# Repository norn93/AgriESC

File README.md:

# AgriESC
A brushless motor driver for small to medium sized motors

This project was forked from and inspired by antonchromjak's MINI4 (Mini VESC: https://github.com/antonchromjak/MINI4) and was practically copied from Benjamin Vedder's Brushless Motor Controller (VESC: https://github.com/vedderb/bldc-hardware). It is an attempt to build a slightly cheaper motor controller for 24 V/10 A motors.

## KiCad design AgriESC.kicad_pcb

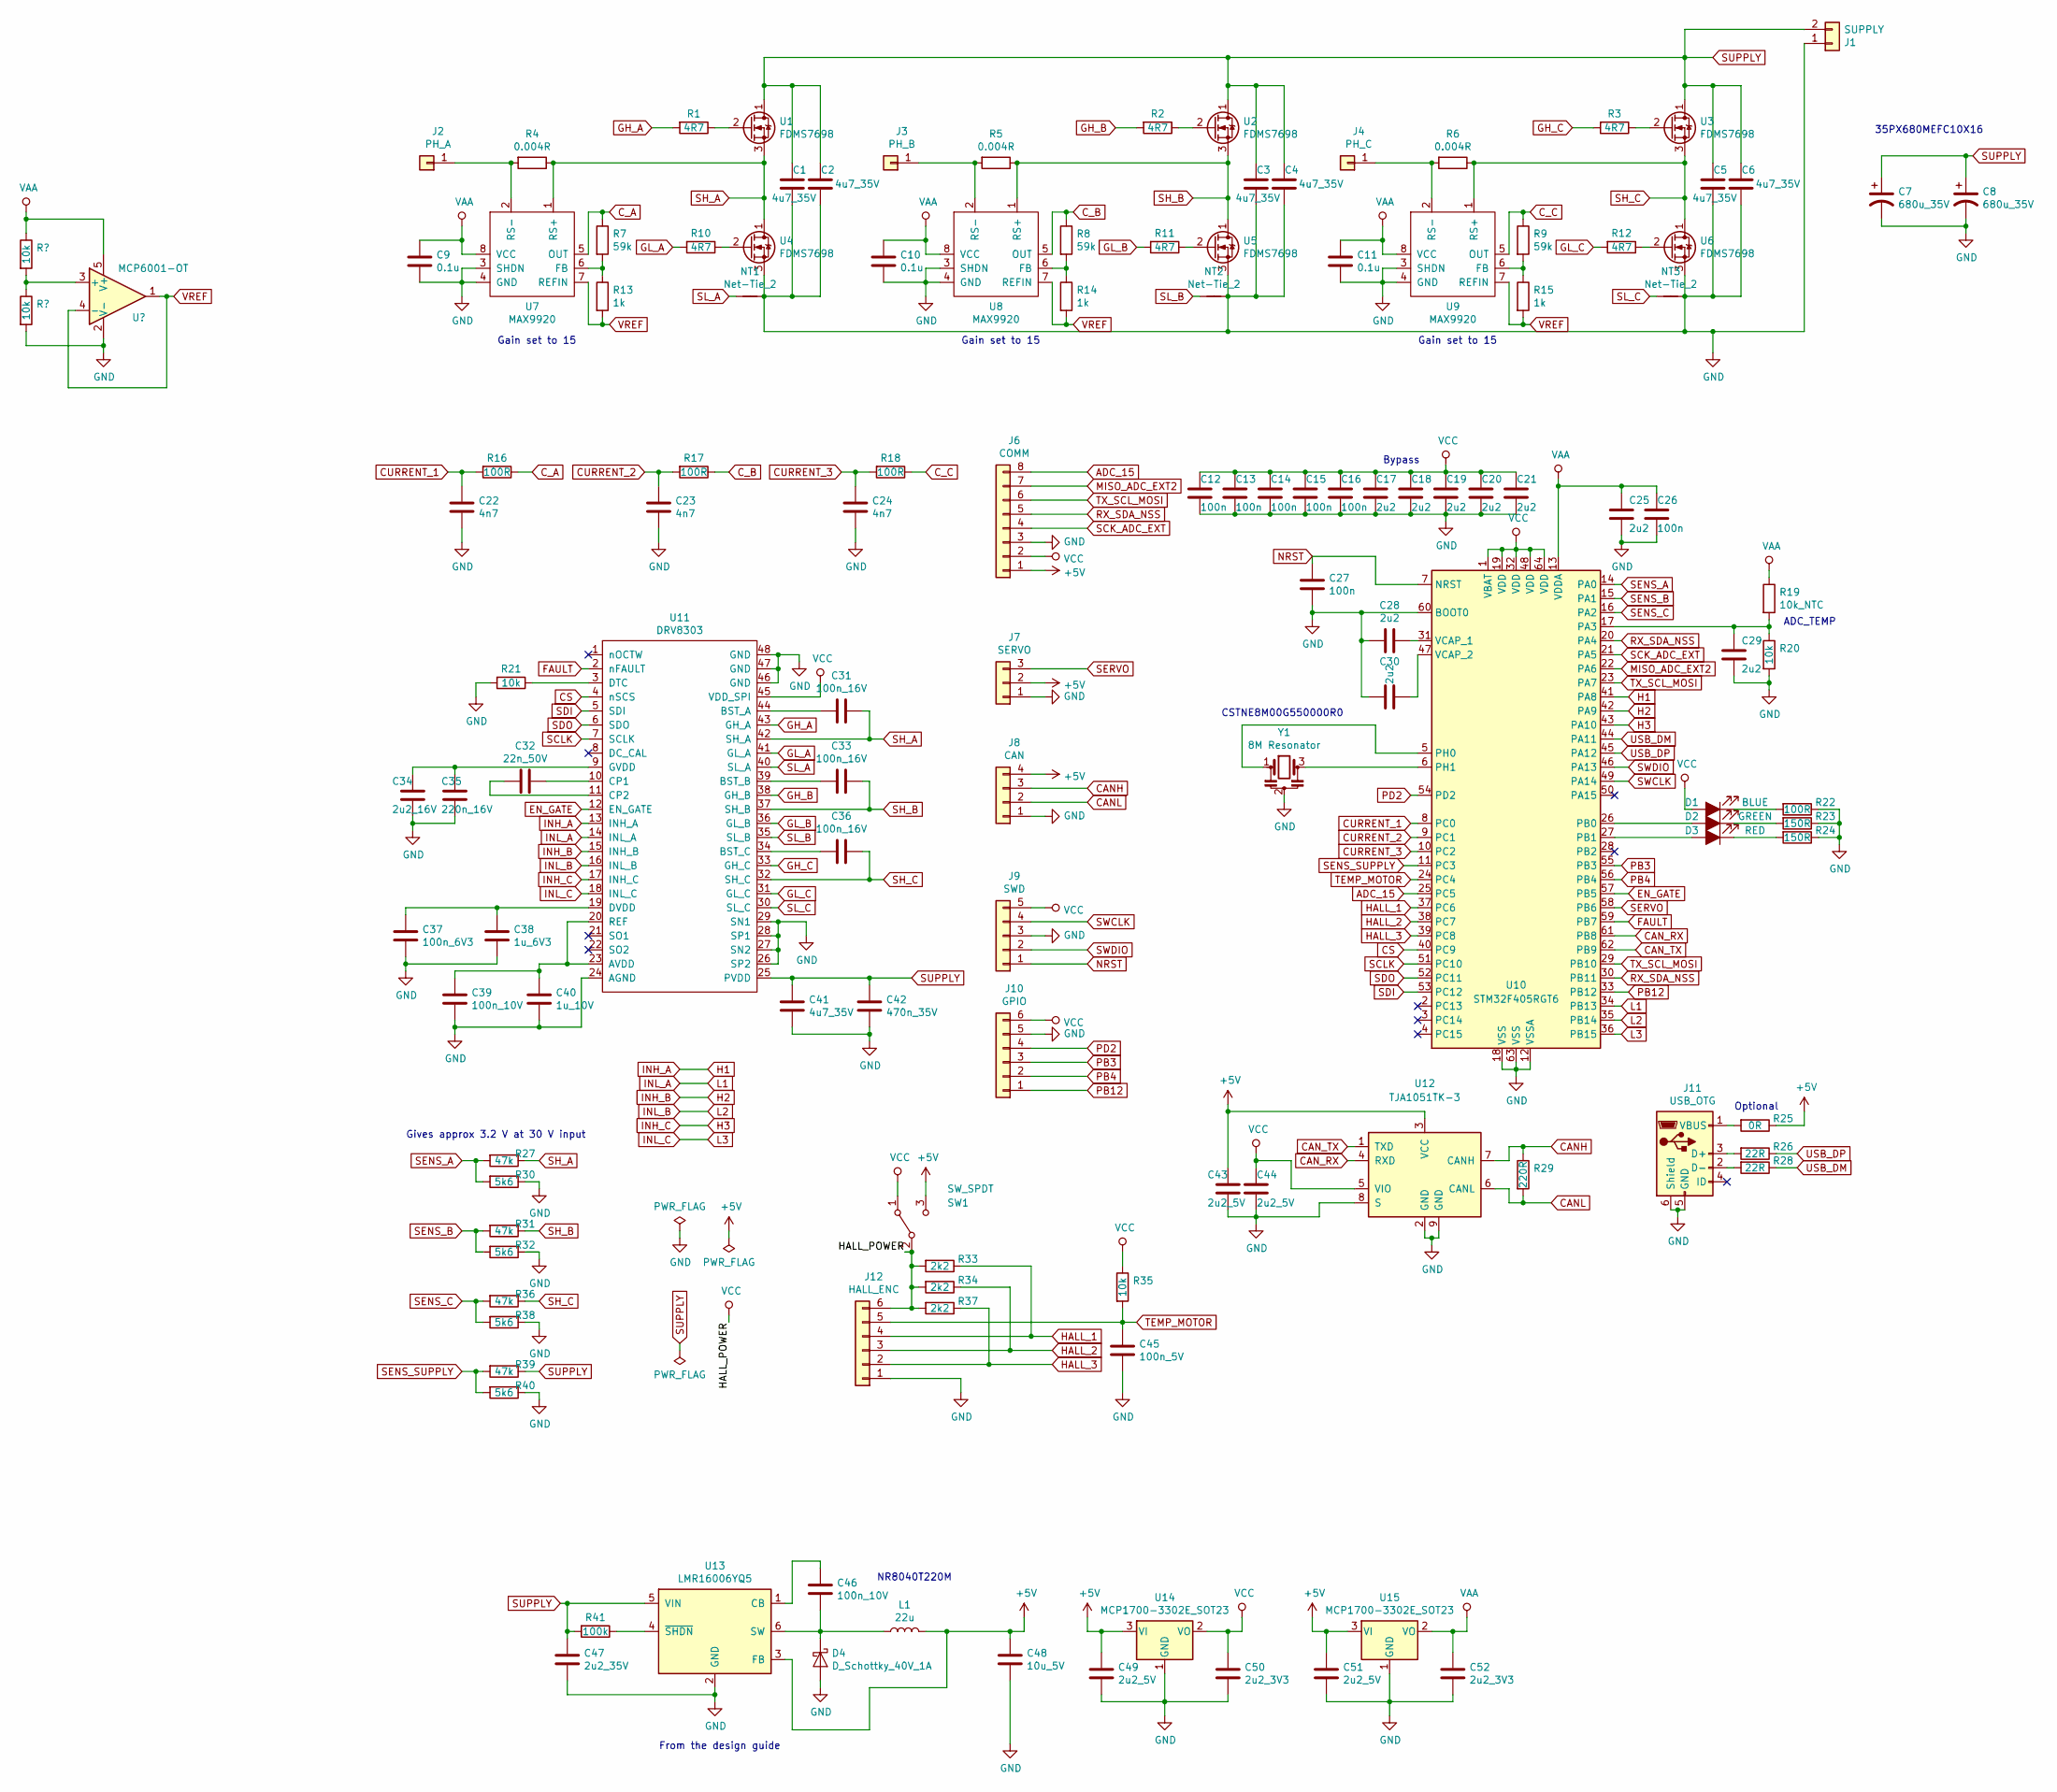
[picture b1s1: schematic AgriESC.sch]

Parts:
C1, C2, C3, C4, C5, C6, C41: 4u7_35V; C_0805_2012Metric_Pad1.15x1.40mm_HandSolder
C7, C8: 680u_35V; CP_Radial_D10.0mm_P5.00mm_Side_Mounted
C9, C10, C11: 0.1u; C_0603_1608Metric_Pad1.05x0.95mm_HandSolder
C12, C13, C14, C15, C16, C26, C27: 100n; C_0603_1608Metric_Pad1.05x0.95mm_HandSolder
C17, C18, C19, C20, C21, C25, C28, C29, C30: 2u2; C_0603_1608Metric_Pad1.05x0.95mm_HandSolder
C22, C23, C24: 4n7; C_0603_1608Metric_Pad1.05x0.95mm_HandSolder
C31, C33, C36: 100n_16V; C_0603_1608Metric_Pad1.05x0.95mm_HandSolder
C32: 22n_50V; C_0603_1608Metric_Pad1.05x0.95mm_HandSolder
C34: 2u2_16V; C_0603_1608Metric_Pad1.05x0.95mm_HandSolder
C35: 220n_16V; C_0603_1608Metric_Pad1.05x0.95mm_HandSolder
C37: 100n_6V3; C_0603_1608Metric_Pad1.05x0.95mm_HandSolder
C38: 1u_6V3; C_0603_1608Metric_Pad1.05x0.95mm_HandSolder
C39, C46: 100n_10V; C_0603_1608Metric_Pad1.05x0.95mm_HandSolder
C40: 1u_10V; C_0603_1608Metric_Pad1.05x0.95mm_HandSolder
C42: 470n_35V; C_0603_1608Metric_Pad1.05x0.95mm_HandSolder
C43, C44, C49, C51: 2u2_5V; C_0603_1608Metric_Pad1.05x0.95mm_HandSolder
C45: 100n_5V; C_0603_1608Metric_Pad1.05x0.95mm_HandSolder
C47: 2u2_35V; C_0603_1608Metric_Pad1.05x0.95mm_HandSolder
C48: 10u_5V; C_0603_1608Metric_Pad1.05x0.95mm_HandSolder
C50, C52: 2u2_3V3; C_0603_1608Metric_Pad1.05x0.95mm_HandSolder
D1: BLUE; LED_0603_1608Metric_Pad1.05x0.95mm_HandSolder
D2: GREEN; LED_0603_1608Metric_Pad1.05x0.95mm_HandSolder
D3: RED; LED_0603_1608Metric_Pad1.05x0.95mm_HandSolder
D4: D_Schottky_40V_1A; D_SOD-123F
J1: SUPPLY; XT30PW-F
J2: PH_A; SolderWirePad_1x01_SMD_5x10mm
J3: PH_B; SolderWirePad_1x01_SMD_5x10mm
J4: PH_C; SolderWirePad_1x01_SMD_5x10mm
J6: COMM; JST_PA_01x08
J7: SERVO; JST_PA_01x03
J8: CAN; JST_PA_01x04
J9: SWD; JST_PA_01x05
J10: GPIO; JST_PA_01x06
J11: USB_OTG; CONN-10118194-0001LF-FCI3
J12: HALL_ENC; JST_PA_01x06
L1: 22u; NR8040T220M
NT1, NT2, NT3: Net-Tie_2; NetTie-2_SMD_Pad0.5mm
R1, R2, R3, R10, R11, R12: 4R7; R_0603_1608Metric_Pad1.05x0.95mm_HandSolder
R4, R5, R6: 0.004R; R_2512_6332Metric_Pad1.52x3.35mm_HandSolder
R7, R8, R9: 59k; R_0603_1608Metric_Pad1.05x0.95mm_HandSolder
R13, R14, R15: 1k; R_0603_1608Metric_Pad1.05x0.95mm_HandSolder
R16, R17, R18, R22: 100R; R_0603_1608Metric_Pad1.05x0.95mm_HandSolder
R19: 10k_NTC; R_0603_1608Metric_Pad1.05x0.95mm_HandSolder
R20, R21, R35: 10k; R_0603_1608Metric_Pad1.05x0.95mm_HandSolder
R23, R24: 150R; R_0603_1608Metric_Pad1.05x0.95mm_HandSolder
R25: 0R; R_0603_1608Metric_Pad1.05x0.95mm_HandSolder
R26, R28: 22R; R_0603_1608Metric_Pad1.05x0.95mm_HandSolder
R27, R31, R36, R39: 47k; R_0603_1608Metric_Pad1.05x0.95mm_HandSolder
R29: 220R; R_0603_1608Metric_Pad1.05x0.95mm_HandSolder
R30, R32, R38, R40: 5k6; R_0603_1608Metric_Pad1.05x0.95mm_HandSolder
R33, R34, R37: 2k2; R_0603_1608Metric_Pad1.05x0.95mm_HandSolder
R41: 100k; R_0603_1608Metric_Pad1.05x0.95mm_HandSolder
SW1: SW_SPDT; SolderJumper-3_P1.3mm_Open_RoundedPad1.0x1.5mm_NumberLabels
U1, U2, U3, U4, U5, U6: FDMS7698
U7, U8, U9: MAX9920
U10: STM32F405RGT6; LQFP-64_10x10mm_P0.5mm
U11: DRV8303
U12: TJA1051TK-3; DFN-8-1EP_3x3mm_Pitch0.65mm
U13: LMR16006YQ5; SOT-23-6
U14, U15: MCP1700-3302E_SOT23; SOT-23
Y1: 8M Resonator; CSTNE8M00G550000R0

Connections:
+5V: C43.1, C48.1, C49.1, C51.1, J6.1, J7.2, J8.4, L1.2, R25.1, SW1.3 (C), U12.3 (VCC), U13.3 (FB), U14.3 (VI), U15.3 (VI); also elsewhere on the board
ADC_15: J6.8, U10.25 (PC5); also elsewhere on the board
CANH: J8.3, R29.1, U12.7 (CANH); also elsewhere on the board
CANL: J8.2, R29.2, U12.6 (CANL); also elsewhere on the board
CAN_RX: U10.61 (PB8), U12.4 (RXD)
CAN_TX: U10.62 (PB9), U12.1 (TXD)
CS: U10.40 (PC9), U11.4 (nSCS)
CURRENT_1: C22.1, R16.2, U10.8 (PC0)
CURRENT_2: C23.1, R17.2, U10.9 (PC1)
CURRENT_3: C24.1, R18.2, U10.10 (PC2)
C_A: R7.1, R16.1, U7.5 (OUT)
C_B: R8.1, R17.1, U8.5 (OUT)
C_C: R9.1, R18.1, U9.5 (OUT)
EN_GATE: U10.57 (PB5), U11.12 (EN_GATE)
FAULT: U10.59 (PB7), U11.2 (nFAULT)
GH_A: R1.2, U11.43 (GH_A)
GH_B: R2.2, U11.38 (GH_B)
GH_C: R3.2, U11.33 (GH_C)
GL_A: R10.2, U11.41 (GL_A)
GL_B: R11.2, U11.36 (GL_B)
GL_C: R12.2, U11.31 (GL_C)
GND: C1.2, C2.2, C3.2, C4.2, C5.2, C6.2, C7.2, C8.2, C9.2, C10.2, C11.2, C12.2, C13.2, C14.2, C15.2, C16.2, C17.2, C18.2, C19.2, C20.2, C21.2, C22.2, C23.2, C24.2, C25.2, C26.2, C27.2, C28.2, C29.2, C30.2, C34.2, C35.2, C37.2, C38.2, C39.2, C40.2, C41.2, C42.2, C43.2, C44.2, C45.2, C47.2, C48.2, C49.2, C50.2, C51.2, C52.2, D4.2 (A), J1.1, J6.3, J7.1, J8.1, J9.3, J10.5, J11.5 (GND), J11.6 (Shield), J12.1, NT1.1, NT2.1, NT3.1, R20.2, R21.2, R22.1, R23.1, R24.1, R30.1, R32.1, R38.1, R40.1, U4.3 (S), U5.3 (S), U6.3 (S), U7.3 (SHDN), U7.4 (GND), U8.3 (SHDN), U8.4 (GND), U9.3 (SHDN), U9.4 (GND), U10.12 (VSSA), U10.18 (VSS), U10.60 (BOOT0), U10.63 (VSS), U11.24 (AGND), U11.26 (SP2), U11.27 (SN2), U11.28 (SP1), U11.29 (SN1), U11.46 (GND), U11.47 (GND), U11.48 (GND), U12.2 (GND), U12.8 (S), U12.9 (GND), U13.2 (GND), U14.1 (GND), U15.1 (GND), Y1.2; also elsewhere on the board
H1: U10.41 (PA8), U11.13 (INH_A)
H2: U10.42 (PA9), U11.15 (INH_B)
H3: U10.43 (PA10), U11.17 (INH_C)
HALL_1: J12.4, R33.1, U10.37 (PC6); also elsewhere on the board
HALL_2: J12.3, R34.1, U10.38 (PC7); also elsewhere on the board
HALL_3: J12.2, R37.1, U10.39 (PC8); also elsewhere on the board
INL_A: U10.34 (PB13), U11.14 (INL_A)
INL_B: U10.35 (PB14), U11.16 (INL_B)
INL_C: U10.36 (PB15), U11.18 (INL_C)
MISO_ADC_EXT2: J6.7, U10.22 (PA6); also elsewhere on the board
NRST: C27.1, J9.1, U10.7 (NRST); also elsewhere on the board
unnamed: C28.1, U10.31 (VCAP_1)
unnamed: C29.1, R19.2, R20.1, U10.17 (PA3)
unnamed: C30.1, U10.47 (VCAP_2)
unnamed: C31.2, U11.44 (BST_A)
unnamed: C32.1, U11.10 (CP1)
unnamed: C32.2, U11.11 (CP2)
unnamed: C33.2, U11.39 (BST_B)
unnamed: C34.1, C35.1, U11.9 (GVDD)
unnamed: C36.2, U11.34 (BST_C)
unnamed: C37.1, C38.1, U11.19 (DVDD)
unnamed: C39.1, C40.1, U11.20 (REF), U11.23 (AVDD)
unnamed: C46.1, D4.1 (K), L1.1, U13.6 (SW)
unnamed: C46.2, U13.1 (CB)
unnamed: D1.1 (K), R22.2
unnamed: D2.1 (K), R23.2
unnamed: D2.2 (A), U10.26 (PB0)
unnamed: D3.1 (K), R24.2
unnamed: D3.2 (A), U10.27 (PB1)
unnamed 51: J2.1, R4.2, U7.2 (RS-); also elsewhere on the board
unnamed 52: J3.1, R5.2, U8.2 (RS-); also elsewhere on the board
unnamed 53: J4.1, R6.2, U9.2 (RS-); also elsewhere on the board
unnamed 54: J11.1 (VBUS), R25.2; also elsewhere on the board
unnamed 55: J11.2 (D-), R28.2; also elsewhere on the board
unnamed 56: J11.3 (D+), R26.2; also elsewhere on the board
unnamed: R1.1, U1.2 (G)
unnamed: R2.1, U2.2 (G)
unnamed: R3.1, U3.2 (G)
unnamed: R10.1, U4.2 (G)
unnamed: R11.1, U5.2 (G)
unnamed: R12.1, U6.2 (G)
unnamed: R7.2, R13.1, U7.6 (FB)
unnamed: R8.2, R14.1, U8.6 (FB)
unnamed: R9.2, R15.1, U9.6 (FB)
unnamed: R21.1, U11.3 (DTC)
unnamed: R41.1, U13.4 (~SHDN)
unnamed: U10.5 (PH0), Y1.1
unnamed: U10.6 (PH1), Y1.3
PB3: J10.3, U10.55 (PB3); also elsewhere on the board
PB4: J10.2, U10.56 (PB4); also elsewhere on the board
PB12: J10.1, U10.33 (PB12); also elsewhere on the board
PD2: J10.4, U10.54 (PD2); also elsewhere on the board
RX_SDA_NSS: J6.5, U10.20 (PA4), U10.30 (PB11); also elsewhere on the board
SCK_ADC_EXT: J6.4, U10.21 (PA5); also elsewhere on the board
SCLK: U10.51 (PC10), U11.7 (SCLK)
SDI: U10.53 (PC12), U11.5 (SDI)
SDO: U10.52 (PC11), U11.6 (SDO)
SENS_A: R27.2, R30.2, U10.14 (PA0)
SENS_B: R31.2, R32.2, U10.15 (PA1)
SENS_C: R36.2, R38.2, U10.16 (PA2)
SENS_SUPPLY: R39.2, R40.2, U10.11 (PC3)
SERVO: J7.3, U10.58 (PB6); also elsewhere on the board
SH_A: C31.1, R4.1, R27.1, U1.3 (S), U4.1 (D), U7.1 (RS+), U11.42 (SH_A)
SH_B: C33.1, R5.1, R31.1, U2.3 (S), U5.1 (D), U8.1 (RS+), U11.37 (SH_B)
SH_C: C36.1, R6.1, R36.1, U3.3 (S), U6.1 (D), U9.1 (RS+), U11.32 (SH_C)
SL_A: NT1.2, U11.40 (SL_A)
SL_B: NT2.2, U11.35 (SL_B)
SL_C: NT3.2, U11.30 (SL_C)
SUPPLY: C1.1, C2.1, C3.1, C4.1, C5.1, C6.1, C7.1, C8.1, C41.1, C42.1, C47.1, J1.2, R39.1, R41.2, U1.1 (D), U2.1 (D), U3.1 (D), U11.25 (PVDD), U13.5 (VIN)
SWCLK: J9.4, U10.49 (PA14); also elsewhere on the board
SWDIO: J9.2, U10.46 (PA13); also elsewhere on the board
TEMP_MOTOR: C45.1, J12.5, R35.2, U10.24 (PC4); also elsewhere on the board
TX_SCL_MOSI: J6.6, U10.23 (PA7), U10.29 (PB10); also elsewhere on the board
USB_DM: R28.1, U10.44 (PA11)
USB_DP: R26.1, U10.45 (PA12)
VAA: C9.1, C10.1, C11.1, C25.1, C26.1, C52.1, R19.1, U7.8 (VCC), U8.8 (VCC), U9.8 (VCC), U10.13 (VDDA), U15.2 (VO); also elsewhere on the board
VCC: C12.1, C13.1, C14.1, C15.1, C16.1, C17.1, C18.1, C19.1, C20.1, C21.1, C44.1, C50.1, D1.2 (A), J6.2, J9.5, J10.6, J12.6, R33.2, R34.2, R35.1, R37.2, SW1.1 (A), SW1.2 (B), U10.1 (VBAT), U10.19 (VDD), U10.32 (VDD), U10.48 (VDD), U10.64 (VDD), U11.45 (VDD_SPI), U12.5 (VIO), U14.2 (VO); also elsewhere on the board
VREF: R13.2, R14.2, R15.2, U7.7 (REFIN), U8.7 (REFIN), U9.7 (REFIN); also elsewhere on the board

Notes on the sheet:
Bypass
Optional
Gain set to 15
ADC_TEMP
From the design guide
Gives approx 3.2 V at 30 V input
CSTNE8M00G550000R0
NR8040T220M
35PX680MEFC10X16

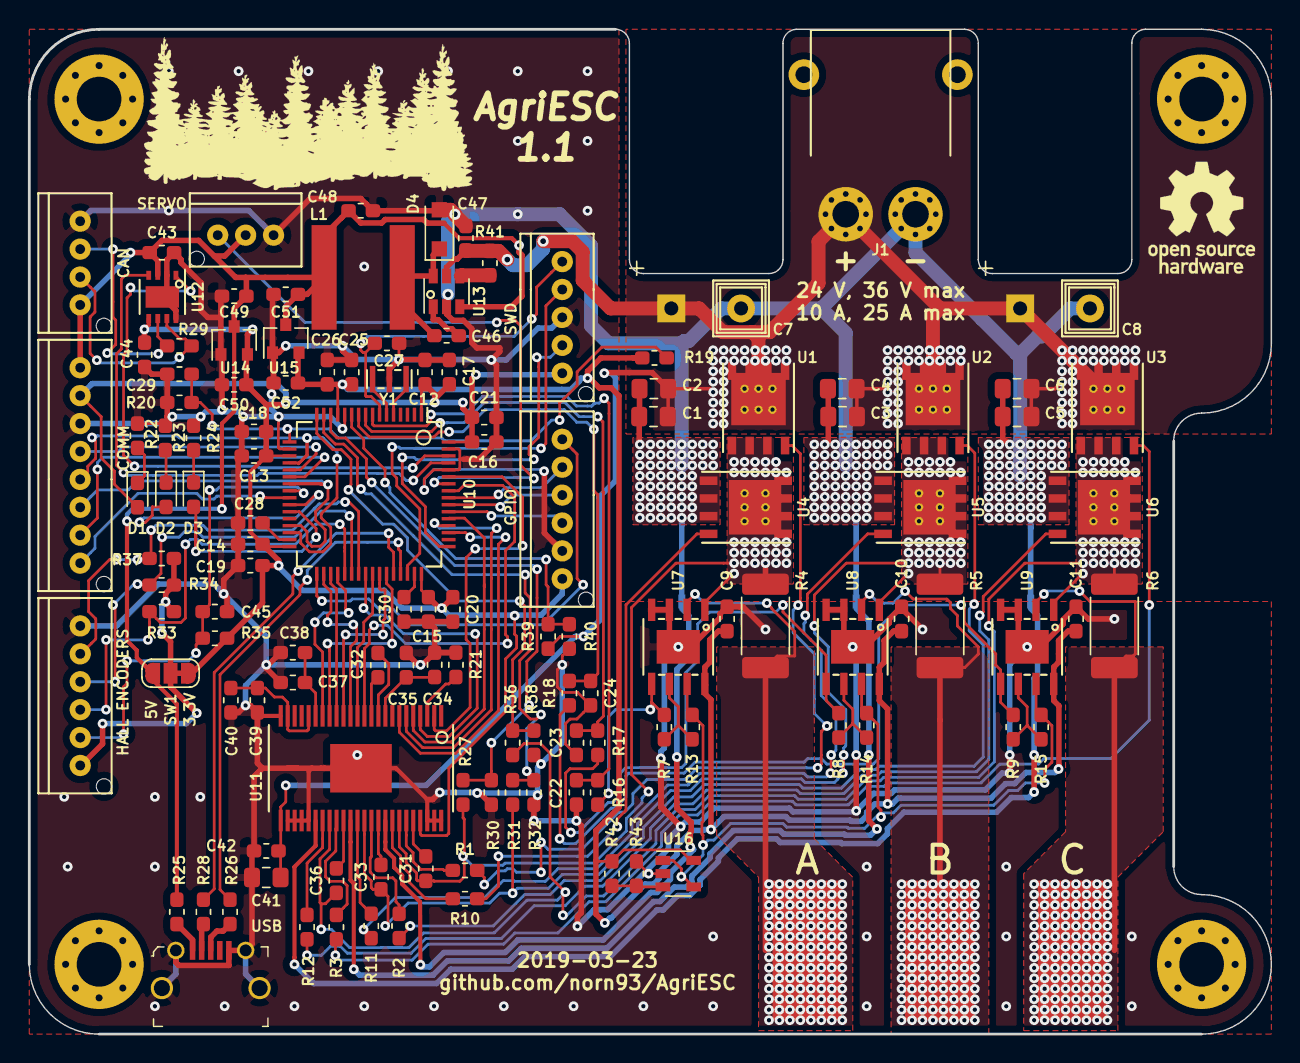
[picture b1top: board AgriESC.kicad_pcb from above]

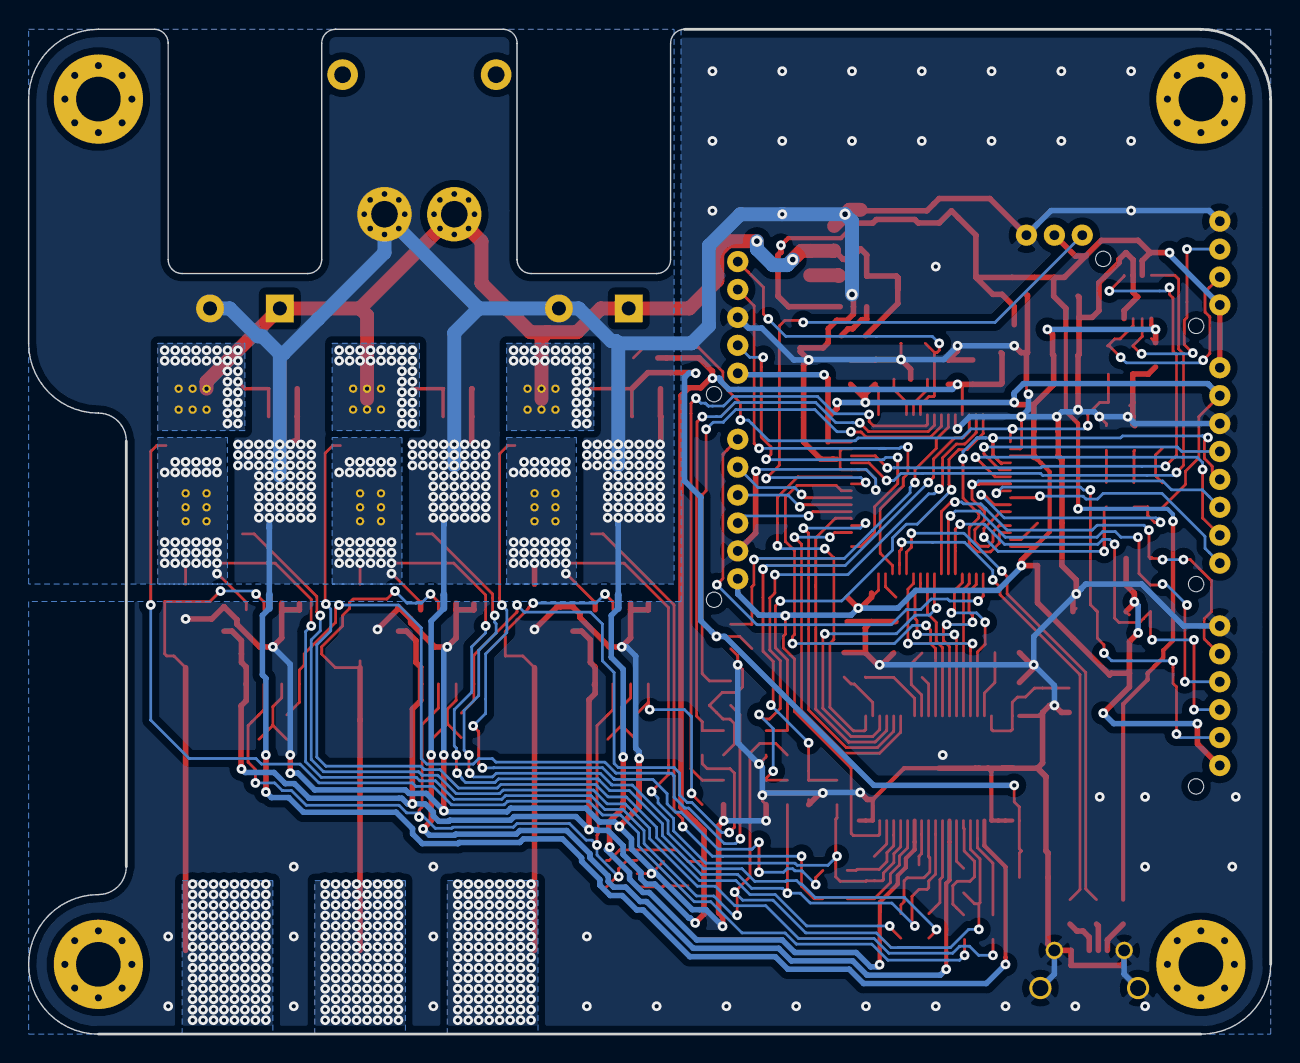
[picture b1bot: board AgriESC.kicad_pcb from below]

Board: 2 copper layers, 89.0 x 72.0 mm, 132 parts (3 on the bottom side), 101 nets.

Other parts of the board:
A: PH_A; SolderWirePad_1x01_SMD_5x10mm
B: PH_B; SolderWirePad_1x01_SMD_5x10mm
C: PH_C; SolderWirePad_1x01_SMD_5x10mm
CAN: CAN; JST_PA_01x04
COMM: COMM; JST_PA_01x08
GPIO: GPIO; JST_PA_01x06
HALL ENCODERS: HALL_ENC; JST_PA_01x06
R42, R43: 10k; R_0603_1608Metric_Pad1.05x0.95mm_HandSolder
SERVO: SERVO; JST_PA_01x03
SWD: SWD; JST_PA_01x05
U16: MCP6001-OT; SOT-23-5
USB: USB_OTG; CONN-10118194-0001LF-FCI3

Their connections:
+5V: CAN.4, COMM.1, SERVO.2; also elsewhere on the board
ADC_15: COMM.8; also elsewhere on the board
CANH: CAN.3; also elsewhere on the board
CANL: CAN.2; also elsewhere on the board
GND: CAN.1, COMM.3, GPIO.5, HALL ENCODERS.1, R43.2, SERVO.1, SWD.3, U16.2, USB.5, USB.6; also elsewhere on the board
HALL_1: HALL ENCODERS.4; also elsewhere on the board
HALL_2: HALL ENCODERS.3; also elsewhere on the board
HALL_3: HALL ENCODERS.2; also elsewhere on the board
MISO_ADC_EXT2: COMM.7; also elsewhere on the board
NRST: SWD.1; also elsewhere on the board
unnamed 51: A.1; also elsewhere on the board
unnamed 52: B.1; also elsewhere on the board
unnamed 53: C.1; also elsewhere on the board
unnamed 54: USB.1; also elsewhere on the board
unnamed 55: USB.2; also elsewhere on the board
unnamed 56: USB.3; also elsewhere on the board
unnamed: R42.2, R43.1, U16.3
PB3: GPIO.3; also elsewhere on the board
PB4: GPIO.2; also elsewhere on the board
PB12: GPIO.1; also elsewhere on the board
PD2: GPIO.4; also elsewhere on the board
RX_SDA_NSS: COMM.5; also elsewhere on the board
SCK_ADC_EXT: COMM.4; also elsewhere on the board
SERVO: SERVO.3; also elsewhere on the board
SWCLK: SWD.4; also elsewhere on the board
SWDIO: SWD.2; also elsewhere on the board
TEMP_MOTOR: HALL ENCODERS.5; also elsewhere on the board
TX_SCL_MOSI: COMM.6; also elsewhere on the board
VAA: R42.1, U16.5; also elsewhere on the board
VCC: COMM.2, GPIO.6, HALL ENCODERS.6, SWD.5; also elsewhere on the board
VREF: U16.1, U16.4; also elsewhere on the board

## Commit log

2018-07-10 Reorganising directory structure for new project
2018-07-10 Added microcontroller
2018-07-10 Added CAN, USB, hall sensors, servo
2018-07-10 Added document detailing current sense op amp comparison
2018-07-10 Added further details of search parameters
2018-07-27 Started adding driver
2018-07-28 First draft of schematic complete
2018-07-29 Started allocating footprints
2018-07-31 Added MAX9920 footprint to schematic
2018-07-31 Created MAX9920 footprint in project library
2018-08-01 Added capacitor voltages, added bulk capacitors for battery power supply, changed crystal, added bypass capacitors for higher frequencies
2018-08-01 Added DRV8303 footprint
2018-08-02 Added footprints for slide switch and FET
2018-08-02 Updated footprints, added analog supply
2018-08-03 Updated footprints to include silkscreen
2018-08-03 Reset annotation
2018-08-03 Created draft net
2018-08-03 Added PA style JST connectors
2018-08-03 Added XT30PW-M battery connector
2018-08-03 Added USB connector
2018-08-03 Started PCB layout
2018-08-03 Updated schematic with new battery supply connector and more MPNs
2018-08-03 Corrected XT30
2018-08-03 Corrected battery connector polarity
2018-08-03 Started work on high current PCB layout
2018-08-05 Fixed footprint vias
2018-08-05 First draft of high current part
2018-08-05 Added a via footprint for heat-sinking
2018-08-06 Added vias to footprint
2018-08-06 Backed up old PCB
2018-08-06 Added new inductor and resonator footprints
2018-08-06 Updated schematic with new components
2018-08-06 Updated PCB layout to be much more compact
2018-08-06 Second draft of high current part of PCB complete
2018-08-07 Adding current sense op amps
2018-11-17 Routed FET side of board, and removed copper layer for heatsink
2018-11-18 Updated resonator footprint to include silkscreen
2018-11-18 Arranged critical microcontroller components, started arranging driver components
2018-11-26 Arranged 5V power stage according to layout guide
2018-11-26 Wired up LDOs
2018-11-26 Added USB wiring
2018-11-26 Finished USB ground
2018-11-26 Added CAN wiring
2018-11-26 Fix to schematic
2018-11-26 Arranged hall sensors
2018-11-26 Wiring for motor driver
2018-11-26 Wiring for microprocessor
2018-11-26 Started arranging components
2018-11-26 Working through the routing
2018-11-27 PCB routing
2018-11-27 Before CAN package update
2018-11-27 More routing, and an adjustment to the USB connector shield/ground
2018-12-01 Routing
2018-12-01 Routed thermistor
2018-12-01 Routing completed! Now cleaning up tracks and increasing width where appropriate
2018-12-01 Widening important traces
2018-12-02 Correcting boundary
2018-12-02 Updated from schematic
2018-12-02 Moved USB and added moutning points
2018-12-02 Added more ground planes to digital section
2018-12-02 Cleaning routing
2018-12-02 Rotated caps
2018-12-02 Stronger traces. Saving progress before trying to reduce board height
2018-12-02 Trying to make board more compact by moving buck converter
2018-12-15 Added a bunch of logos, and a simple footprint for a side-mounted electrolytic capacitor
2018-12-15 Images for logos
2018-12-15 Version 1.0 completed
2018-12-16 Exported gerber files for fabrication
2019-03-16 Version 1
2019-03-16 Updated LED resistors
2019-03-16 Updated LMR16006YQ to fixed 5V version, removed feedback resistors
2019-03-16 Fixed earthing on LMR
2019-03-16 Added some more vias
2019-03-16 Updated USB footprint
2019-03-23 Added new MAX9920 VREFIN
2019-03-23 Annotations
2019-03-23 Generated new net
2019-03-23 Multiple small changes, all PCB layout related
2019-03-23 Version 1.1
2019-03-24 Added IBOM 1.1
2019-10-03 Added gcode for making top and bottom of case
2019-10-27 New gcode for cutting heatsink
